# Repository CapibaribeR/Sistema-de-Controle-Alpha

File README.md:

# Sistema de Controle Alpha Motor Scooter

- Área: **Elétrica**
- Subárea: **Powertrain**
- Responsável:
  - **Nathan Pinheiro, nathan.pinheiro@ufpe.br**
- Período de trabalho: **23/06/2022~~xx/xx/xxxx**
- Link para pasta no drive: **[Sistema de Controle do Motor](https://drive.google.com/drive/u/0/folders/1gA4DVZMdsN3olOmKE0vOmF9ez8T_oJ0C)**

## Objetivos

O sistema de controle Alpha é o mais simples sistema de controle dos motores e inversores pela DCU, unidade de controle dinâmica do veículo. O sistema Alpha 
recebe dados de 2 sensores que medem o deslocamente do pedal do acelerador (APPS) e de um sensor que mede o deslocamento do pedal do freio (BSE). Mediante os
dados recebidos e uma lógica de controle, o sistema Alpha deve mandar a requisitada velocidade que o piloto está pedindo (ao pressionar o pedal) para o inversor,
este responsável por então ajustar o motor para a velocidade desejada. O diagrama abaixo representa a visão geral do sistema de controle alpha.

## Desenvolvimento

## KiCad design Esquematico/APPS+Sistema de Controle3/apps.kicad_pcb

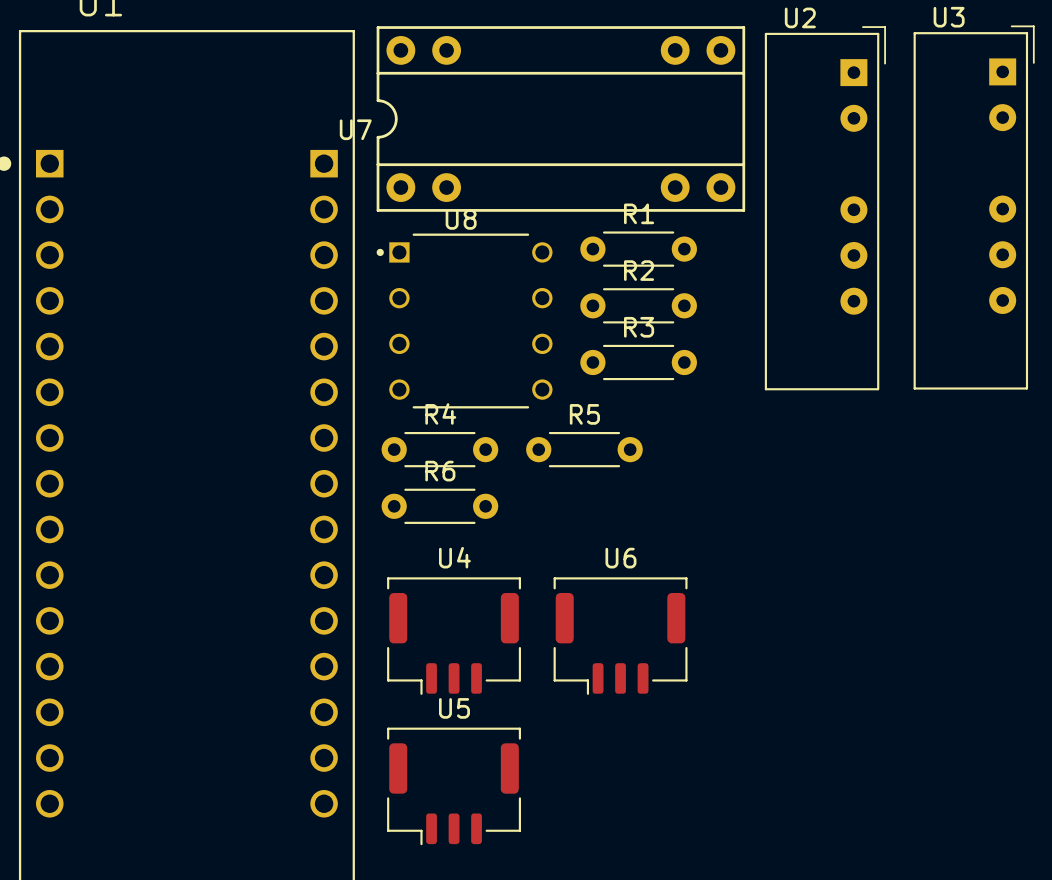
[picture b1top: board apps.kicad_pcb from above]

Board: 2 copper layers, 14 parts (0 on the bottom side), 7 nets, no tracks yet.

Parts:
R1, R3, R5: 22k; R_Axial_DIN0204_L3.6mm_D1.6mm_P5.08mm_Horizontal
R2, R4, R6: 100k; R_Axial_DIN0204_L3.6mm_D1.6mm_P5.08mm_Horizontal
U1: STM32F303K8; MODULE_NUCLEO-F303K8
U2, U3: A0515S-2W; Converter_DCDC_muRata_NMAxxxxSC_THT
U4, U6: RTY120LVNAX; Molex_CLIK-Mate_502382-0370_1x03-1MP_P1.25mm_Vertical
U5: Inversor; Molex_CLIK-Mate_502382-0370_1x03-1MP_P1.25mm_Vertical
U7: ISO124; 8
U8: LM358P; DIP794W45P254L959H508Q8

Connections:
/+5V: U4.1, U6.1
/S1_APPS: R1.1, R2.2
/S2_APPS: R3.1, R4.2
GND: R2.1, R4.1, U4.2, U6.2
unnamed: R1.2, U4.3
unnamed: R3.2, U6.3
unnamed: R5.2, R6.2

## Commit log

2022-06-24 Primeiro commit
2022-06-24 Adicionando platformIO
2022-06-24 Adicionando README.md
2022-06-24 Adição do código no PlatformIO
2022-06-27 Adicionando uma nova versão do código
    A pasta de sistema de controle que é onde está o código real feito no MBED
2022-06-28 Juncao BSE+APPS
2022-06-29 adicionar BSE
2022-06-29 Pinagem do sensor bse
2022-06-29 Erro no BSE+APPS
2022-06-30 Erro no CHECK
2022-07-04 Adicao do flag_plausibility
2022-07-04 Iniciando mudanca
2022-07-05 Erro brusco
2022-07-05 Salvando para mudar
2022-07-06 Analise de erro resolvida
2022-07-07 Resolvido ERROR, resolvendo plausibility
